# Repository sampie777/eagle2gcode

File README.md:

# Eagle 2 gCode

This project is developed for the purpose of manufacturing homemade PCBs. The idea is to have minimal file input, minimal user interaction, and maximum result.

As I'm not good with polygon maths, Flatcam is used for the outlining of the traces etc. for milling. To minimize user input for Flatcam, a set of Flatcam commands are created in the first screen of this GUI. The user just has to paste these command into Flatcam and that's all interaction with Flatcam. 

This project does the rest of the processing, like offset, mirroring, iterations, producing the correct gcode, etc. 

This project is a continuous developing project, as my experience with the manufacturing increases, I'll update this project. 

All files and settings remain on the client's computer. There's no backend server. 

I do not take any responsibility for any damages occurred from using this program and the produces gcode. It is the user's responsibility to check that the gcode is correct and won't damage any equipment.

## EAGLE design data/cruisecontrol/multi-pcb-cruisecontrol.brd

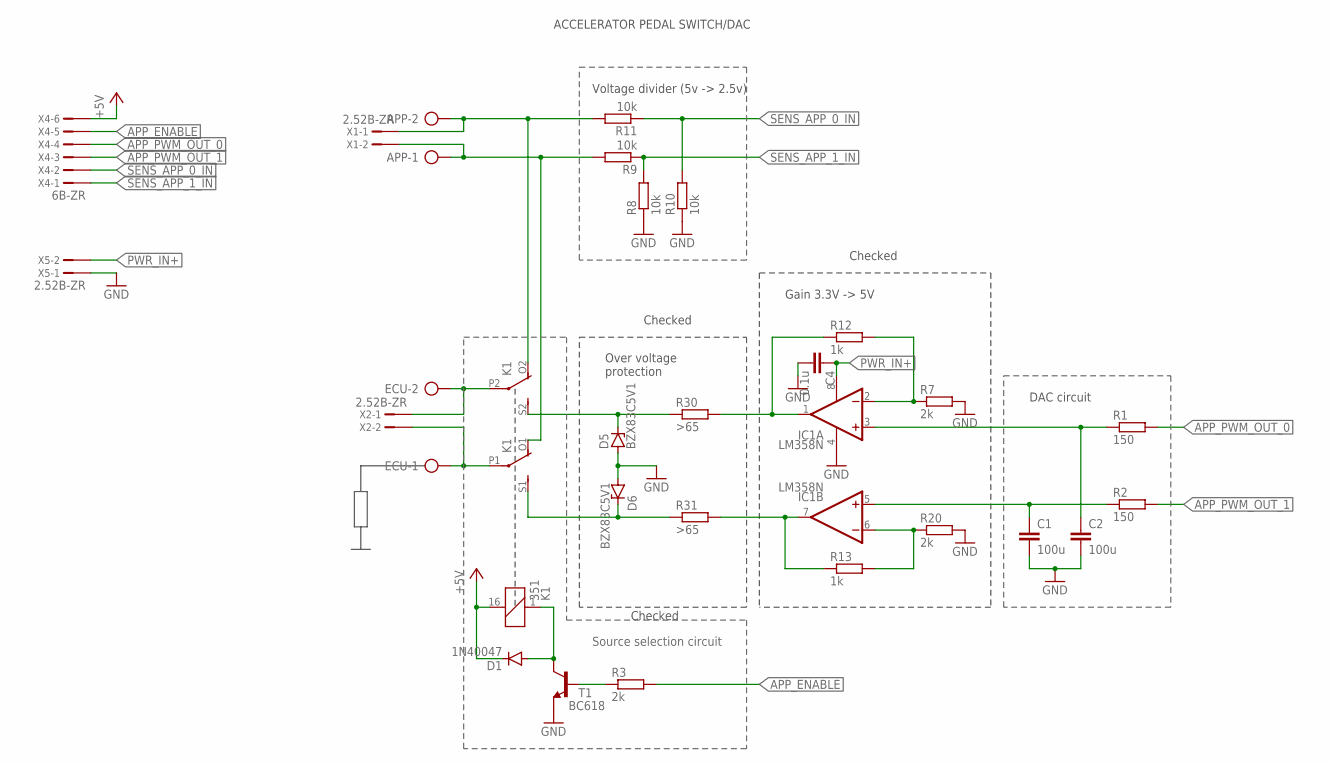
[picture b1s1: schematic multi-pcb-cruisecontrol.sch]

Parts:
APP: AK300/2
C1, C2: 100u; C025-050X050
C4: 0.1u; C025-050X050
D1: 1N40047; DO41-7.6
D5, D6: BZX83C5V1; DO41Z7.6
ECU: AK300/2
IC1: LM358N; DIL08
K1: 351
R1, R2: 150; 0207/7
R3, R7, R20: 2k; 0207/7
R8, R9, R10, R11: 10k; 0207/7
R12, R13: 1k; 0207/7
R30, R31: >65; 0207/7
T1: BC618; TO92-EBC
X1, X2, X5: 2.52B-ZR; B2B-ZR2.5
X4: 6B-ZR; B6B-ZR2.5

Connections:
+5V: D1.C, K1.16 (2), X4.6
APP_0_IN: APP.2, K1.O2 (O), R11.2, X1.1
APP_1_IN: APP.1, K1.O1 (O), R9.2, X1.2
APP_ENABLE: R3.2, X4.5
APP_PWM_OUT_0: R1.2, X4.4
APP_PWM_OUT_1: R2.2, X4.3
GND: C1.2, C2.2, C4.2, D5.A, D6.A, IC1.4 (V-), R7.2, R8.1, R10.1, R20.2, T1.E, X5.1
unnamed: D1.A, K1.1, T1.C
unnamed: R3.1, T1.B
unnamed: D6.C, K1.S1 (S), R31.1
unnamed: IC1.1 (OUT), R12.1, R30.2
unnamed: ECU.2, K1.P2, X2.1
unnamed: ECU.1, K1.P1, X2.2
unnamed: C2.1, IC1.3 (+IN), R1.1
unnamed: C1.1, IC1.5 (+IN), R2.1
unnamed: IC1.2 (-IN), R7.1, R12.2
unnamed: IC1.6 (-IN), R13.2, R20.1
unnamed: D5.C, K1.S2 (S), R30.1
unnamed: IC1.7 (OUT), R13.1, R31.2
PWR_IN+: C4.1, IC1.8 (V+), X5.2
SENS_APP_0_IN: R10.2, R11.1, X4.2
SENS_APP_1_IN: R8.2, R9.1, X4.1

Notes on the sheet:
Voltage divider (5v -> 2.5v)
DAC circuit
Source selection circuit
ACCELERATOR PEDAL SWITCH/DAC
Gain 3.3V -> 5V
Over voltage protection
Checked

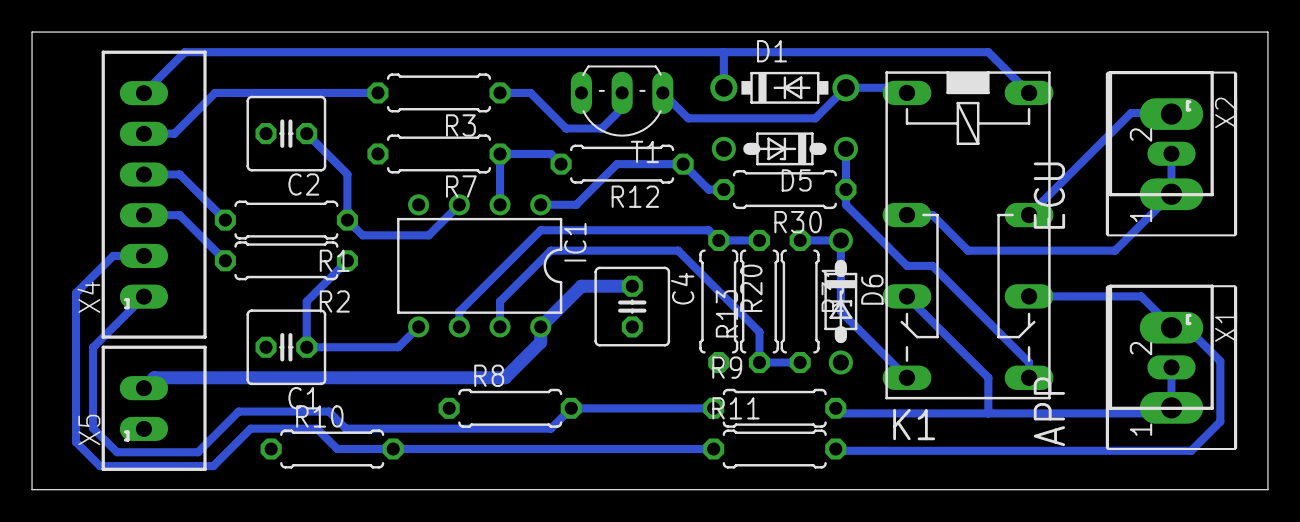
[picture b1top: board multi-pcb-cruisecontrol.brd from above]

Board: 2 copper layers, 77.1 x 28.6 mm, 28 parts (0 on the bottom side), 22 nets.

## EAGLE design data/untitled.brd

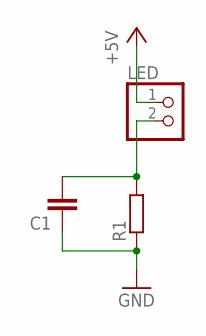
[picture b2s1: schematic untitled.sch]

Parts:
C1: C-EU025-040X050; C025-040X050
LED: PINHD-1X2; 1X02
R1: R-EU_0204/7; 0204/7

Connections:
+5V: LED.1
GND: C1.1, R1.1
unnamed: C1.2, LED.2, R1.2

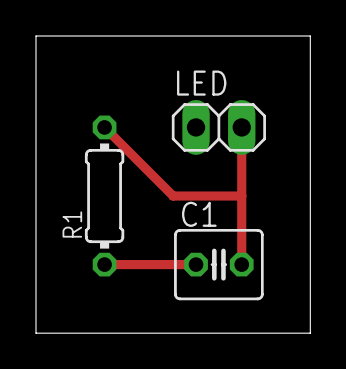
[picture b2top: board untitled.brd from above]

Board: 2 copper layers, 15.2 x 16.5 mm, 3 parts (0 on the bottom side), 2 nets.

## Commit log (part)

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2024-01-09 Created EAGLE source files
2024-01-09 frontend: initial commit
2024-01-09 frontend: created upload screen
2024-01-09 frontend: process drill file
2024-01-09 frontend: process profile file
2024-01-09 frontend: process job file
2024-01-09 frontend: process copper file
2024-01-09 frontend: process gerber files
2024-01-09 frontend: implemented project context
2024-01-09 frontend: implemented basic renderer.
2024-01-10 frontend: implemented first step of board parser.
2024-01-10 frontend: refactored types
2024-01-10 frontend: very basic display of board
2024-01-10 frontend: some graphic improvements
2024-01-10 frontend: draw component outlines and pads.
2024-01-10 draw drills
2024-01-10 draw the PCB itself
2024-01-11 created flatcam setting component
2024-01-11 created button to generate flatcam commands
2024-01-11 implemented commands for generating flatcam commands. Only missing project properties.
2024-01-15 added docker
2024-01-15 added release script
2024-01-15 version release: 0.1.0
2024-01-15 next development version
2024-01-15 fixed docker tag
2024-01-15 version release: 0.1.1
2024-01-16 setup for new tactic: only use flatcam for generating trace outlines, and let our GUI do the rest (offset, iterations, gcode, etc.) WIP
2024-01-16 show grid
2024-01-16 generate drill and drill allignment code
2024-01-16 show drills in renderer
2024-01-16 highlight alignment drills
2024-01-16 show generated files as download links
2024-01-16 added offset and mirroring for copper traces
2024-01-16 added top and bottom for traces.
2024-01-16 version release: 0.2.0
2024-01-17 improved file download buttons. added cutout profile config
2024-01-17 fixed file name
2024-01-17 cutout profile configuration will influence the renderer
2024-01-17 added project name. use drills if no other sources for dimensions are available
2024-01-17 made project and config persistence
2024-01-17 made alignment hole more distinguishable
2024-01-17 show alignment hole locations
2024-01-17 version release: 0.3.0
2024-01-18 added checklist
2024-01-18 improved readme
2024-01-18 improved checklist for drilling
2024-01-18 Fixed 3D camera which couldn't zoom and move right.
2024-01-18 add rotation to drill file based on actual alignment hole locations.
2024-01-18 drill alignment holes first to complete the check
2024-01-18 updated gcode script for drill with better countdown
2024-01-18 version release: 0.4.0
2024-01-18 trying to debug/fix drilling alignment
2024-01-19 fixed drilling alignment
2024-01-19 improved gui
2024-01-19 don't download empty files
2024-01-19 better way of calculating alignment holes as far apart as possible
2024-01-19 add alignment holes to silkscreen setup. improve trace to gcode generator by auto detecting if a trace can be drawn continuously.
2024-01-19 implemented alignment hole offset calculation for silkscreen
2024-01-19 some silkscreen improvements
2024-01-19 version release: 0.5.0
2024-01-26 feat: Live reload canvas when settings change
2024-01-26 feat: show offset drill holes for debug
2024-01-26 feat: Include example project button
2024-01-26 version release: 0.6.0
2024-07-13 fix(import): Fixed bug when importing board file.
2024-07-13 fix(gui): Don't show endless decimals.
2024-09-13 feat(gui): Separate traces top/bottom in viewer.
2024-09-13 version release: 0.6.1
2024-09-16 handle negative values and hide silkscreen for these values.
2024-09-17 Use a SolidJS store for the config so the render updates instantly.
2024-09-17 Fixed typescript settings
2024-09-17 Updated SolidJS to latest
2024-09-17 Show expected duration for print files.
2024-09-17 version release: 0.7.0
2024-09-17 Updated checklist with manual drill method
2024-09-17 Fix crash if no drills are specified
2024-09-17 Also include travel time in time calculation
2024-09-19 Added option to ignore out of bound traces.
2024-09-19 Updated layout of canvas options
2024-09-19 added project version
2024-09-19 version release: 0.8.0
2024-09-20 added loading icons
2024-09-21 Added ground plane info
2024-09-21 Added time estimate for acid duration. Also styled download buttons.
2024-09-21 version release: 0.8.1
2024-09-25 feat: Preview file (if download is not working) using ctrl+click.
2024-09-25 version release: 0.8.2
2024-09-26 fix: Recalculate print time when traces out of bounds changes.
